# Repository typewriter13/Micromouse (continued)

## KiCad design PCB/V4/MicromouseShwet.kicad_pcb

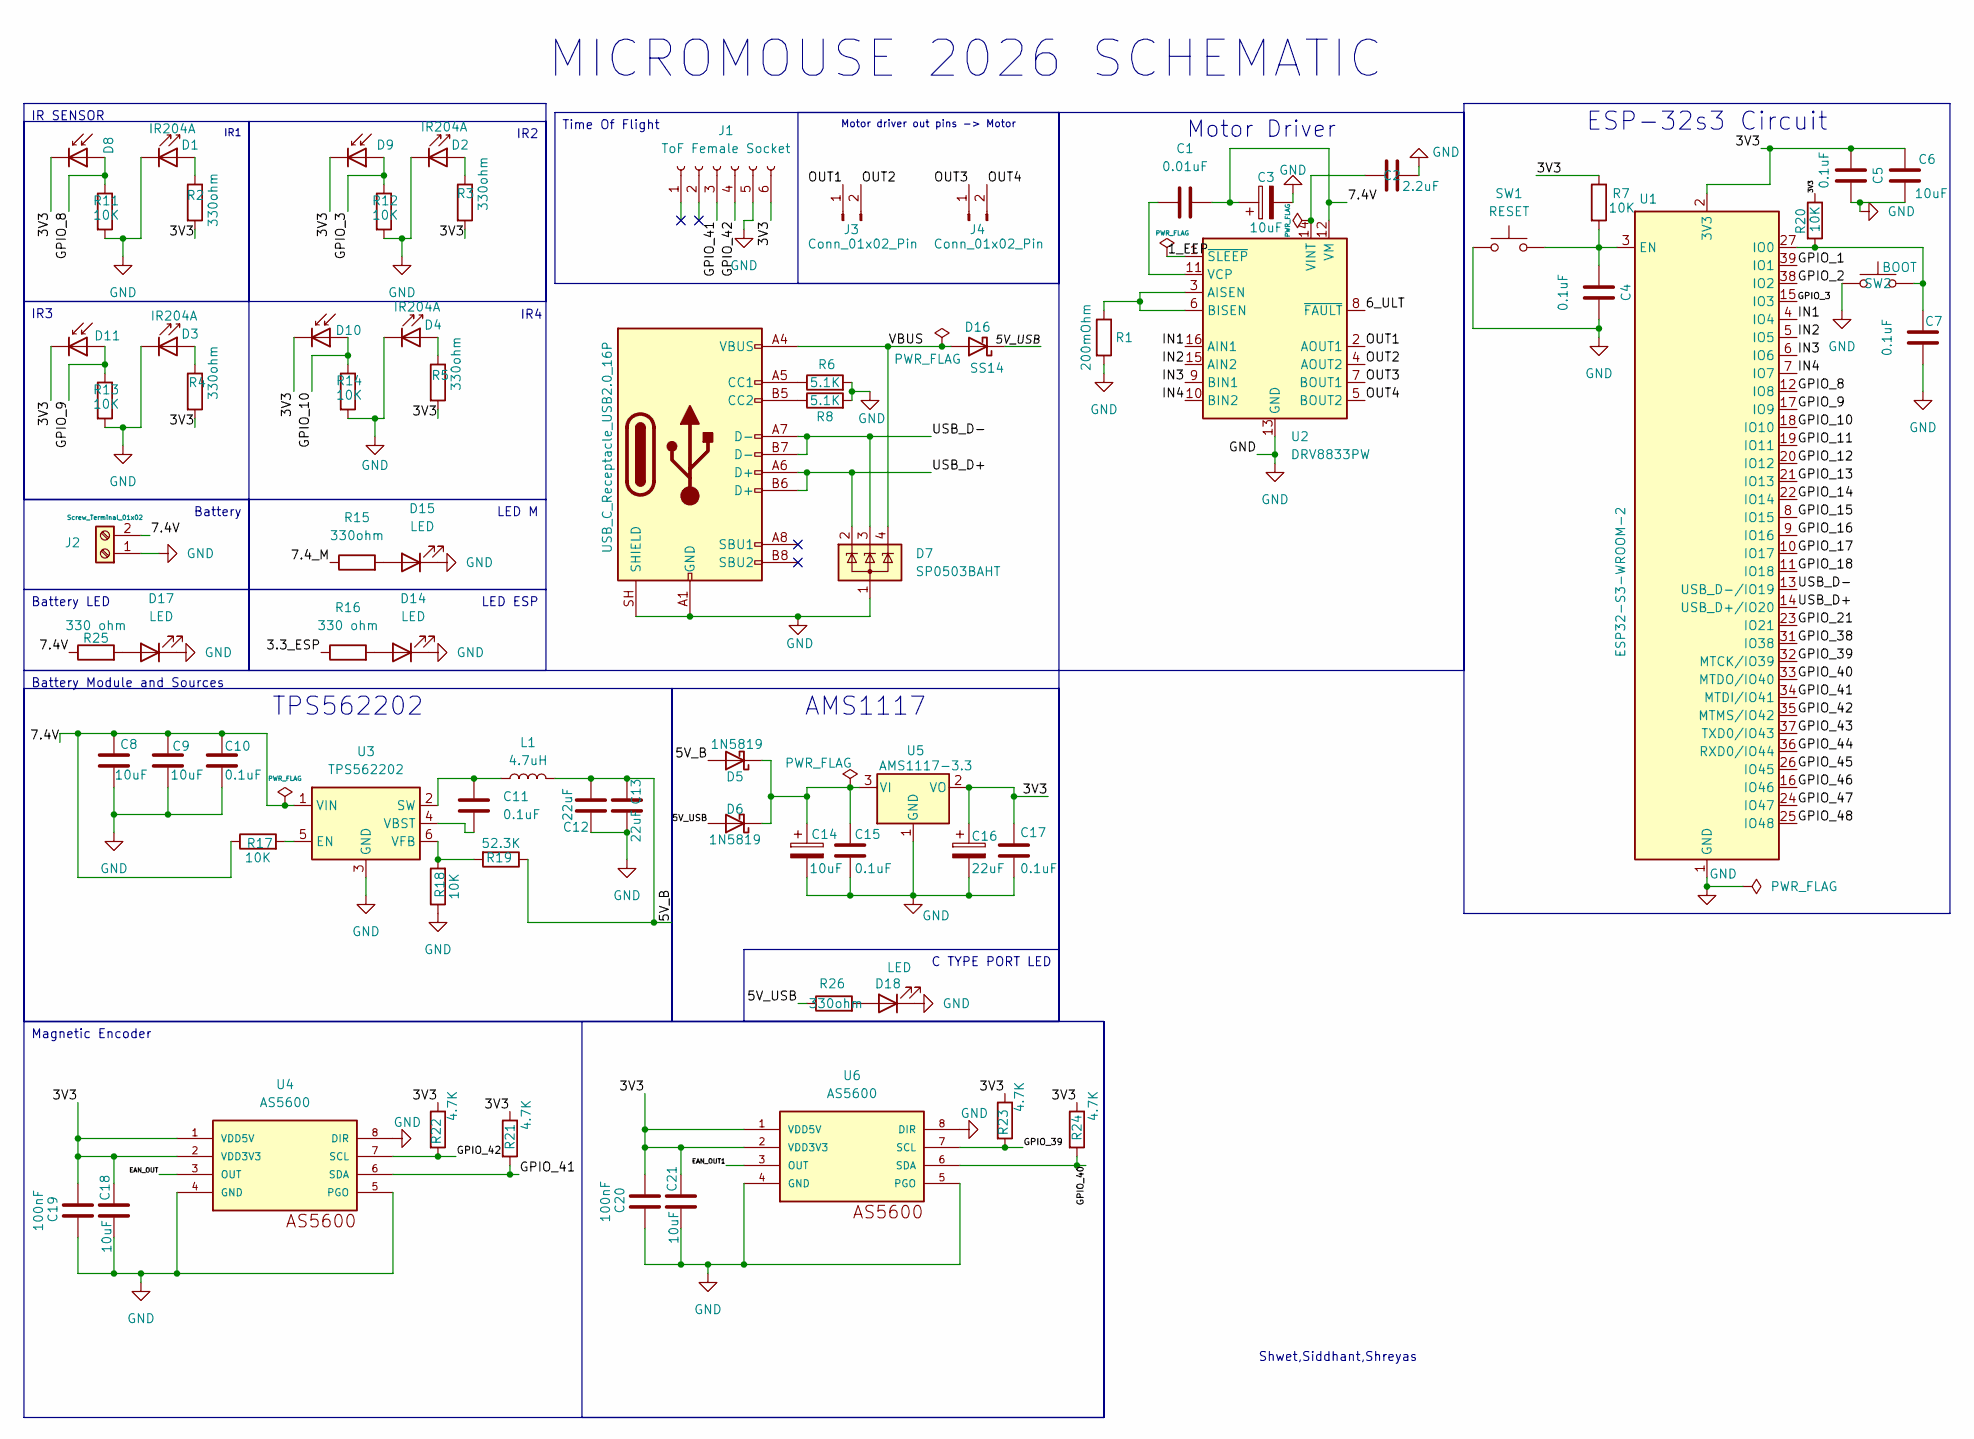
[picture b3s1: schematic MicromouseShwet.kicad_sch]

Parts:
C1: 0.01uF; C_0805_2012Metric
C2: 2.2uF; C_0805_2012Metric
C3, C6, C8, C9, C14, C18, C21: 10uF; C_0805_2012Metric
C4, C5, C7, C10, C11, C15, C17: 0.1uF; C_0805_2012Metric
C12, C13, C16: 22uF; C_0805_2012Metric
C19, C20: 100nF; C_0805_2012Metric
D1, D2, D3, D4: IR204A; LED_D3.0mm_IRBlack
D5, D6: 1N5819; D_3220_8050Metric
D7: SP0503BAHT; SOT-143
D8, D9, D10, D11: D_Photo; LED_D3.0mm
D14, D15, D17, D18: LED; LED_0805_2012Metric
D16: SS14; D_SMA
J1: ToF Female Socket; PinSocket_1x06_P1.00mm_Vertical_SMD_Pin1Left
J2: Screw_Terminal_01x02; JST_EH_S2B-EH_1x02_P2.50mm_Horizontal
J3, J4: Conn_01x02_Pin; JST_EH_S2B-EH_1x02_P2.50mm_Horizontal
J5: USB_C_Receptacle_USB2.0_16P; USB_C_Receptacle_GCT_USB4105-xx-A_16P_TopMnt_Horizontal
L1: 4.7uH; L_Sunlord_MWSA0603S
R1: 200mOhm; R_0805_2012Metric
R2, R3, R4, R5, R15, R26: 330ohm; R_0805_2012Metric
R6, R8: 5.1K; R_0805_2012Metric
R7, R11, R12, R13, R14, R17, R18, R20: 10K; R_0805_2012Metric
R16, R25: 330 ohm; R_0805_2012Metric
R19: 52.3K; R_0805_2012Metric
R21, R22, R23, R24: 4.7K; R_0805_2012Metric
SW1: RESET; SW_Push_SPST_NO_Alps_SKRK
SW2: BOOT; SW_Push_SPST_NO_Alps_SKRK
U1: ESP32-S3-WROOM-2
U2: DRV8833PW; TSSOP-16_4.4x5mm_P0.65mm
U3: TPS562202; SOT-563
U4, U6: AS5600; SOIC8
U5: AMS1117-3.3; SOT-223-3_TabPin2

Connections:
/1_EEP: U2.1 (~SLEEP)
/3.3_ESP: R16.1
/3V3: C5.2, C6.1, C16.1, C17.1, C18.1, C19.1, C20.1, C21.1, D8.1 (K), D9.1 (K), D10.1 (K), D11.1 (K), J1.6, R2.2, R3.2, R4.2, R5.2, R7.1, R20.1, R21.1, R22.1, R23.1, R24.1, U1.2 (3V3), U4.1 (VDD5V), U4.2 (VDD3V3), U5.2 (VO), U6.1 (VDD5V), U6.2 (VDD3V3)
/5V_B: C12.1, C13.1, D5.2 (A), L1.2, R19.1
/5V_USB: D6.2 (A), D16.1 (K), R26.1
/6_ULT: U2.8 (~FAULT)
/7.4V: C1.2, C3.1, C8.1, C9.1, C10.1, J2.2, R17.1, R25.1, U2.12 (VM), U3.1 (VIN)
/7.4_M: R15.1
/EAN_OUT: U4.3 (OUT)
/EAN_OUT1: U6.3 (OUT)
/GPIO_1: U1.39 (IO1)
/GPIO_2: U1.38 (IO2)
/GPIO_3: D9.2 (A), R12.1, U1.15 (IO3)
/GPIO_8: D8.2 (A), R11.1, U1.12 (IO8)
/GPIO_9: D11.2 (A), R13.1, U1.17 (IO9)
/GPIO_10: D10.2 (A), R14.1, U1.18 (IO10)
/GPIO_11: U1.19 (IO11)
/GPIO_12: U1.20 (IO12)
/GPIO_13: U1.21 (IO13)
/GPIO_14: U1.22 (IO14)
/GPIO_15: U1.8 (IO15)
/GPIO_16: U1.9 (IO16)
/GPIO_17: U1.10 (IO17)
/GPIO_18: U1.11 (IO18)
/GPIO_21: U1.23 (IO21)
/GPIO_38: U1.31 (IO38)
/GPIO_39: R23.2, U1.32 (MTCK/IO39), U6.7 (SCL)
/GPIO_40: R24.2, U1.33 (MTDO/IO40), U6.6 (SDA)
/GPIO_41: J1.3, R21.2, U1.34 (MTDI/IO41), U4.6 (SDA)
/GPIO_42: J1.4, R22.2, U1.35 (MTMS/IO42), U4.7 (SCL)
/GPIO_43: U1.37 (TXD0/IO43)
/GPIO_44: U1.36 (RXD0/IO44)
/GPIO_45: U1.26 (IO45)
/GPIO_46: U1.16 (IO46)
/GPIO_47: U1.24 (IO47)
/GPIO_48: U1.25 (IO48)
/IN1: U1.4 (IO4), U2.16 (AIN1)
/IN2: U1.5 (IO5), U2.15 (AIN2)
/IN3: U1.6 (IO6), U2.9 (BIN1)
/IN4: U1.7 (IO7), U2.10 (BIN2)
/OUT1: J3.1, U2.2 (AOUT1)
/OUT2: J3.2, U2.4 (AOUT2)
/OUT3: J4.1, U2.7 (BOUT1)
/OUT4: J4.2, U2.5 (BOUT2)
/USB_D+: D7.2 (K), J5.A6 (D+), J5.B6 (D+), U1.14 (USB_D+/IO20)
/USB_D-: D7.3 (K), J5.A7 (D-), J5.B7 (D-), U1.13 (USB_D-/IO19)
/VBUS: D7.4 (K), D16.2 (A), J5.A4 (VBUS), J5.A9 (VBUS), J5.B4 (VBUS), J5.B9 (VBUS)
GND: C2.2, C3.2, C4.1, C5.1, C6.2, C7.1, C8.2, C9.2, C10.2, C12.2, C13.2, C14.2, C15.2, C16.2, C17.2, C18.2, C19.2, C20.2, C21.2, D1.1 (K), D2.1 (K), D3.1 (K), D4.1 (K), D7.1 (A), D14.1 (K), D15.1 (K), D17.1 (K), D18.1 (K), J1.5, J2.1, J5.A1 (GND), J5.A12 (GND), J5.B1 (GND), J5.B12 (GND), J5.SH (SHIELD), R1.2, R6.2, R8.2, R11.2, R12.2, R13.2, R14.2, R18.1, SW1.1, SW2.1, U1.1 (GND), U1.40 (GND), U1.41 (GND), U2.13 (GND), U3.3 (GND), U4.4 (GND), U4.5 (PGO), U4.8 (DIR), U5.1 (GND), U6.4 (GND), U6.5 (PGO), U6.8 (DIR)
unnamed: D1.2 (A), R2.1
unnamed: D2.2 (A), R3.1
unnamed: D3.2 (A), R4.1
unnamed: D4.2 (A), R5.1
unnamed: C14.1, C15.1, D5.1 (K), D6.1 (K), U5.3 (VI)
unnamed: D14.2 (A), R16.2
unnamed: D15.2 (A), R15.2
unnamed: D17.2 (A), R25.2
unnamed: D18.2 (A), R26.2
unnamed: J5.A5 (CC1), R6.1
unnamed: J5.B5 (CC2), R8.1
unnamed: C4.2, R7.2, SW1.2, U1.3 (EN)
unnamed: C7.2, R20.2, SW2.2, U1.27 (IO0)
unnamed: R1.1, U2.3 (AISEN), U2.6 (BISEN)
unnamed: C1.1, U2.11 (VCP)
unnamed: C2.1, U2.14 (VINT)
unnamed: R17.2, U3.5 (EN)
unnamed: C11.1, L1.1, U3.2 (SW)
unnamed: C11.2, U3.4 (VBST)
unnamed: R18.2, R19.2, U3.6 (VFB)

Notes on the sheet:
MICROMOUSE 2026 SCHEMATIC
Shwet,Siddhant,Shreyas
IR4
Magnetic Encoder
ESP-32s3 Circuit
IR1
LED ESP
Battery Module and Sources
Motor driver out pins -> Motor
IR3
LED M
IR2
Battery LED
AMS1117
Battery
C TYPE PORT LED
Motor Driver
TPS562202
IR SENSOR
Time Of Flight

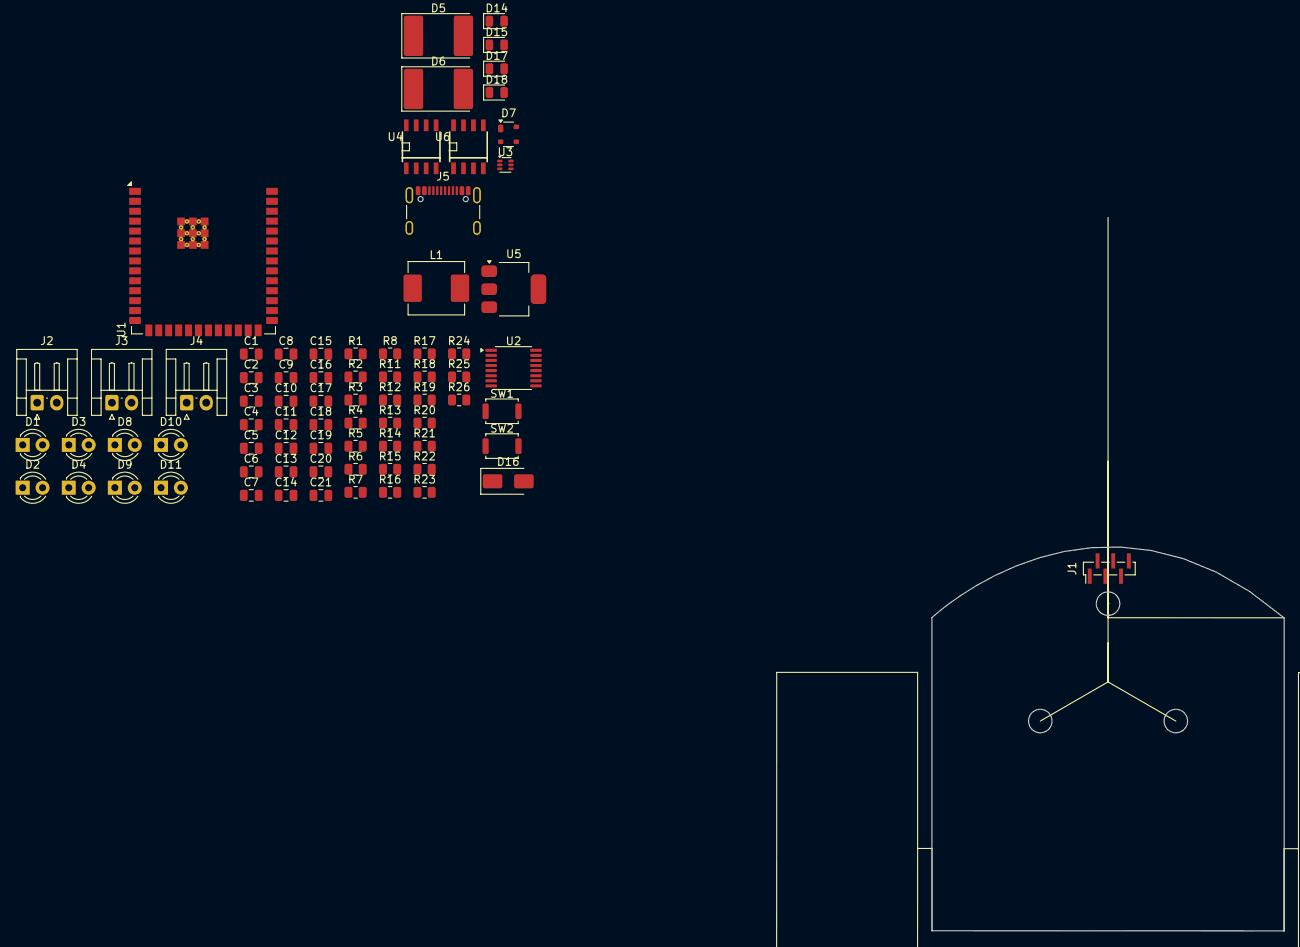
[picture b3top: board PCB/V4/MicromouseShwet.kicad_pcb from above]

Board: 2 copper layers, 45.0 x 49.0 mm, 75 parts (0 on the bottom side), 44 nets.

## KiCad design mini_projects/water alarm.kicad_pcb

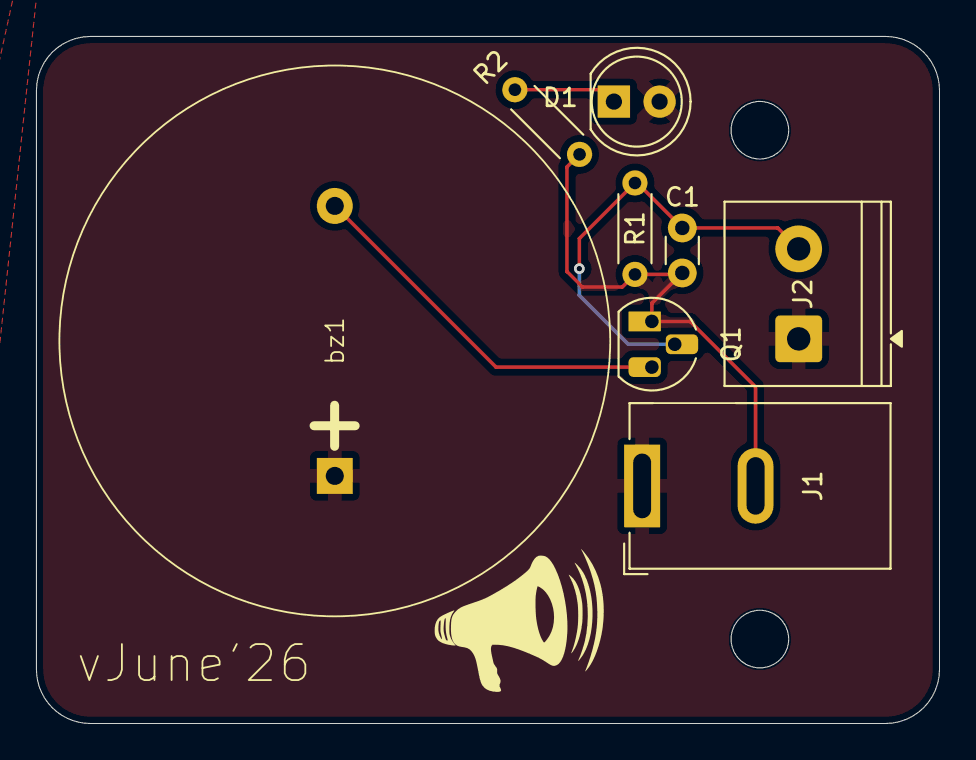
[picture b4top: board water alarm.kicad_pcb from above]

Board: 2 copper layers, 50.2 x 38.2 mm, 8 parts (0 on the bottom side), 5 nets.

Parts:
C1: 1nF; C_Disc_D3.0mm_W1.6mm_P2.50mm
D1: LED_Small_Filled; LED_D5.0mm
J1: Jack-DC; BarrelJack_GCT_DCJ200-10-A_Horizontal
J2: Screw_Terminal_01x02; TerminalBlock_Phoenix_PT-1,5-2-5.0-H_1x02_P5.00mm_Horizontal
Q1: 2N7000; TO-92_HandSolder
R1: 10M; R_Axial_DIN0204_L3.6mm_D1.6mm_P5.08mm_Horizontal
R2: 6.8K; R_Axial_DIN0204_L3.6mm_D1.6mm_P5.08mm_Horizontal
bz1: buzzer; Buzzer_D30mm_H20mm_P15mm_668-1652-ND_Al-3035-TT-12V-R

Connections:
/Gate: C1.1, J2.2, Q1.2 (G), R1.1
GND: C1.2, J1.2, Q1.1 (S), R1.2, R2.2
unnamed: D1.1 (K), R2.1
unnamed: Q1.3 (D), bz1.2 (-)
VCC: D1.2 (A), J1.1, J2.1, bz1.1 (+)

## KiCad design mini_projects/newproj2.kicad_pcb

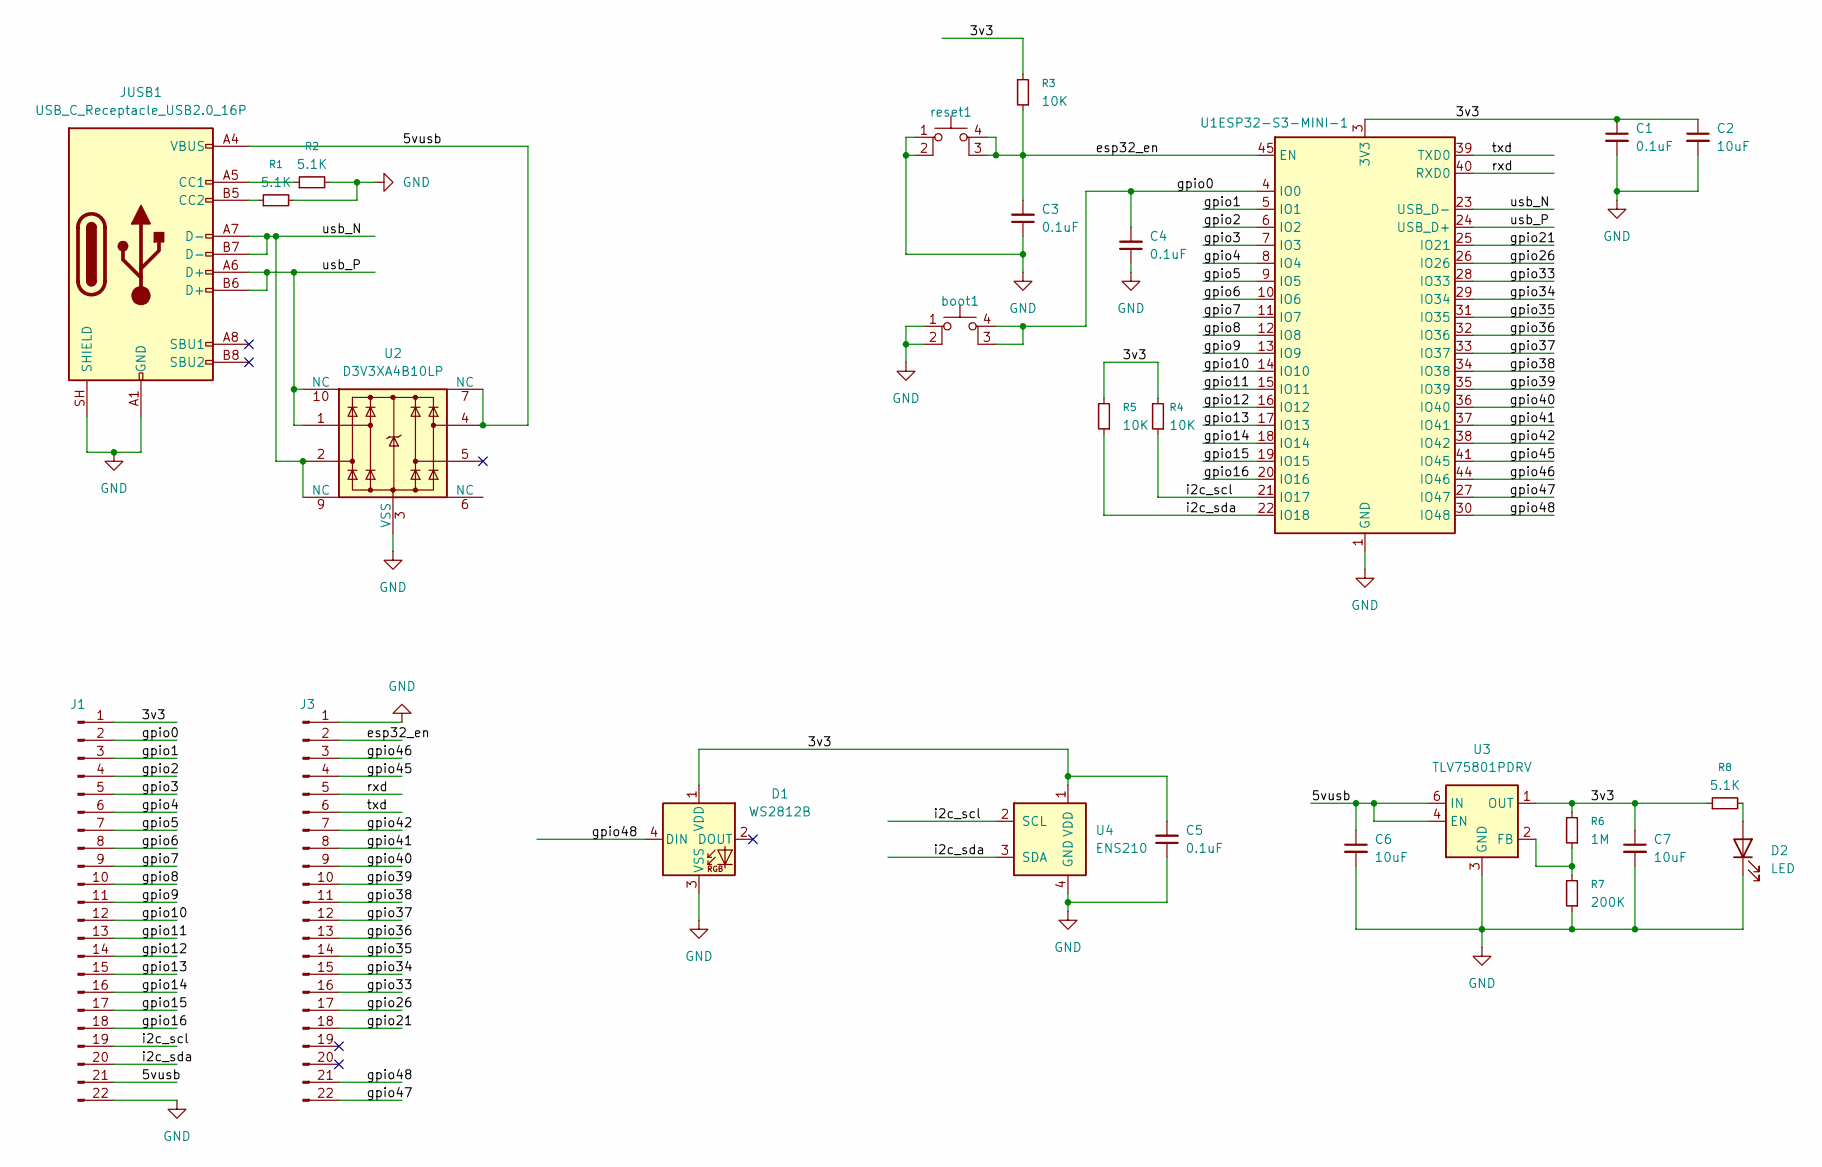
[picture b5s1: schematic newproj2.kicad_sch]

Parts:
C1, C3, C4, C5: 0.1uF; C_0603_1608Metric
C2, C6, C7: 10uF; C_0603_1608Metric
D1: WS2812B; LED_WS2812B_PLCC4_5.0x5.0mm_P3.2mm
D2: LED; LED_0603_1608Metric
J1, J3: Conn_01x22_Pin; PinHeader_1x22_P2.54mm_Vertical
JUSB1: USB_C_Receptacle_USB2.0_16P; USB_C_Receptacle_GCT_USB4105-xx-A_16P_TopMnt_Horizontal
R1, R2, R8: 5.1K; R_0603_1608Metric
R3, R4, R5: 10K; R_0603_1608Metric
R6: 1M; R_0603_1608Metric
R7: 200K; R_0603_1608Metric
U1: ESP32-S3-MINI-1; ESP32-S2-MINI-1
U2: D3V3XA4B10LP; Diodes_UDFN-10_1x2.5mm_P0.5mm
U3: TLV75801PDRV; WSON-6-1EP_2x2mm_P0.65mm_EP1x1.6mm
U4: ENS210; AMS_QFN-4-1EP_2x2mm_P0.95mm_EP0.7x1.6mm
boot1: SW_SPST_PTS810
reset1: SW_SPST_PTS810

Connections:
/5vusb: C6.1, J1.21, JUSB1.A4 (VBUS), JUSB1.A9 (VBUS), JUSB1.B4 (VBUS), JUSB1.B9 (VBUS), U2.4, U2.7 (NC), U3.4 (EN), U3.6 (IN)
/<NO NET>: C1.1, C2.1, C5.2, C7.1, D1.1 (VDD), J1.1, R3.2, R4.2, R5.2, R6.2, R8.1, U1.3 (3V3), U3.1 (OUT), U4.1 (VDD)
/esp32_en: C3.2, J3.2, R3.1, U1.45 (EN), reset1.3 (K), reset1.4 (A)
/gpio0: C4.2, J1.2, U1.4 (IO0), boot1.3 (K), boot1.4 (A)
/gpio1: J1.3, U1.5 (IO1)
/gpio2: J1.4, U1.6 (IO2)
/gpio3: J1.5, U1.7 (IO3)
/gpio4: J1.6, U1.8 (IO4)
/gpio5: J1.7, U1.9 (IO5)
/gpio6: J1.8, U1.10 (IO6)
/gpio7: J1.9, U1.11 (IO7)
/gpio8: J1.10, U1.12 (IO8)
/gpio9: J1.11, U1.13 (IO9)
/gpio10: J1.12, U1.14 (IO10)
/gpio11: J1.13, U1.15 (IO11)
/gpio12: J1.14, U1.16 (IO12)
/gpio13: J1.15, U1.17 (IO13)
/gpio14: J1.16, U1.18 (IO14)
/gpio15: J1.17, U1.19 (IO15)
/gpio16: J1.18, U1.20 (IO16)
/gpio21: J3.18, U1.25 (IO21)
/gpio26: J3.17, U1.26 (IO26)
/gpio33: J3.16, U1.28 (IO33)
/gpio34: J3.15, U1.29 (IO34)
/gpio35: J3.14, U1.31 (IO35)
/gpio36: J3.13, U1.32 (IO36)
/gpio37: J3.12, U1.33 (IO37)
/gpio38: J3.11, U1.34 (IO38)
/gpio39: J3.10, U1.35 (IO39)
/gpio40: J3.9, U1.36 (IO40)
/gpio41: J3.8, U1.37 (IO41)
/gpio42: J3.7, U1.38 (IO42)
/gpio45: J3.4, U1.41 (IO45)
/gpio46: J3.3, U1.44 (IO46)
/gpio47: J3.22, U1.27 (IO47)
/gpio48: D1.4 (DIN), J3.21, U1.30 (IO48)
/i2c_scl: J1.19, R4.1, U1.21 (IO17), U4.2 (SCL)
/i2c_sda: J1.20, R5.1, U1.22 (IO18), U4.3 (SDA)
/rxd: J3.5, U1.40 (RXD0)
/txd: J3.6, U1.39 (TXD0)
/usb_N: JUSB1.A7 (D-), JUSB1.B7 (D-), U1.23 (USB_D-), U2.2, U2.9 (NC)
/usb_P: JUSB1.A6 (D+), JUSB1.B6 (D+), U1.24 (USB_D+), U2.1, U2.10 (NC)
GND: C1.2, C2.2, C3.1, C4.1, C5.1, C6.2, C7.2, D1.3 (VSS), D2.1 (K), J1.22, J3.1, JUSB1.A1 (GND), JUSB1.A12 (GND), JUSB1.B1 (GND), JUSB1.B12 (GND), JUSB1.SH (SHIELD), R1.2, R2.2, R7.1, U1.1 (GND), U1.2 (GND), U1.42 (GND), U1.43 (GND), U1.46 (GND), U1.47 (GND), U1.48 (GND), U1.49 (GND), U1.50 (GND), U1.51 (GND), U1.52 (GND), U1.53 (GND), U1.54 (GND), U1.55 (GND), U1.56 (GND), U1.57 (GND), U1.58 (GND), U1.59 (GND), U1.60 (GND), U1.61 (GND), U1.62 (GND), U1.63 (GND), U1.64 (GND), U1.65 (GND), U2.3 (VSS), U2.8 (VSS), U3.3 (GND), U3.7 (GND), U4.4 (GND), U4.5 (GND), boot1.1, boot1.2, reset1.1, reset1.2
unnamed: D2.2 (A), R8.2
unnamed: JUSB1.A5 (CC1), R2.1
unnamed: JUSB1.B5 (CC2), R1.1
unnamed: R6.1, R7.2, U3.2 (FB)

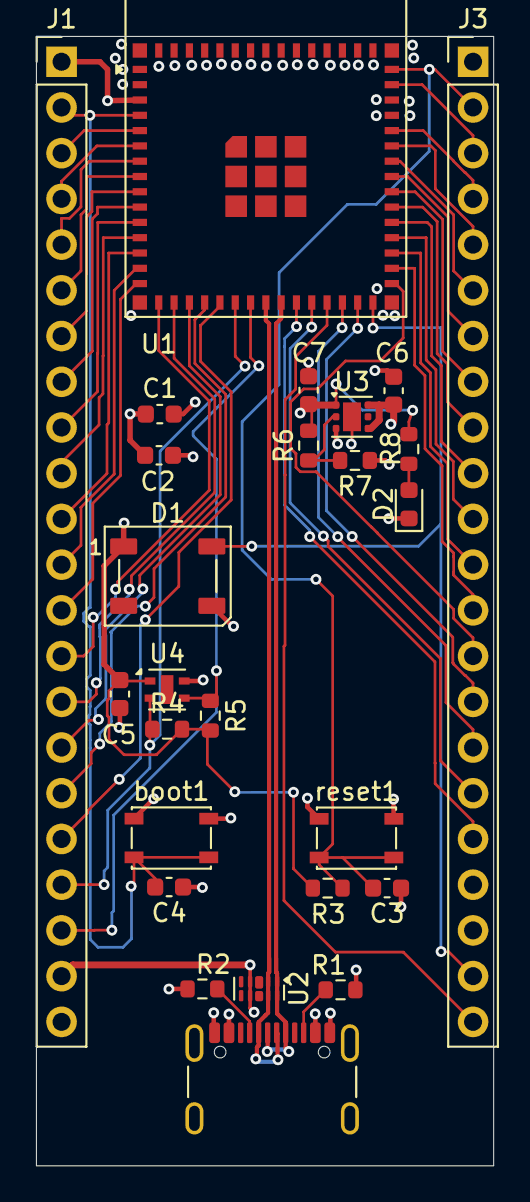
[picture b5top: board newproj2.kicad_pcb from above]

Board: 4 copper layers, 25.4 x 62.7 mm, 26 parts (0 on the bottom side), 47 nets.

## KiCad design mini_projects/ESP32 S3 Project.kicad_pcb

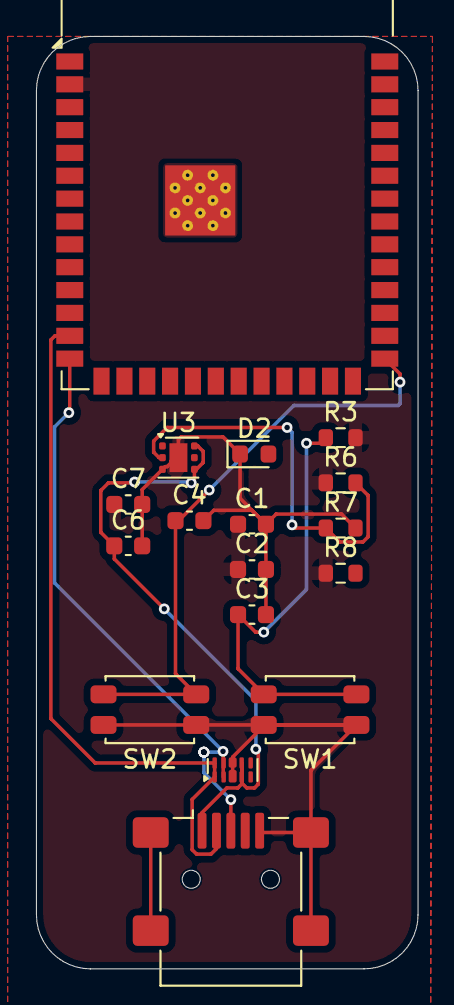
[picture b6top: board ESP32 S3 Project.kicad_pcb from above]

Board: 2 copper layers, 21.2 x 51.8 mm, 17 parts (0 on the bottom side), 9 nets.

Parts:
C1, C3, C4: 0.1uF; C_0603_1608Metric
C2, C6, C7: 10uF; C_0603_1608Metric
D2: LED; LED_0603_1608Metric
J1: USB_B_Micro; USB_Mini-B_Lumberg_2486_01_Horizontal
R3: 10k; R_0603_1608Metric
R6: 1M; R_0603_1608Metric
R7: 200K; R_0603_1608Metric
R8: 5.1K; R_0603_1608Metric
SW1: RESET; SW_SPST_EVQP2_MiddlePushTravel_H2.5mm
SW2: BOOT; SW_SPST_EVQP2_MiddlePushTravel_H2.5mm
U1: ESP32-S3-WROOM-1
U2: D3V3XA4B10LP; Diodes_UDFN-10_1x2.5mm_P0.5mm
U3: TLV75801PDRV; WSON-6-1EP_2x2mm_P0.65mm_EP1x1.6mm

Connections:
/3V3: C1.1, C2.1, C7.1, R3.2, R6.1, R8.1, U1.2 (3V3), U3.1 (OUT)
/5VUSB: C6.1, J1.1 (VBUS), U2.4, U2.7 (NC), U3.4 (EN), U3.6 (IN)
/ESP32_EN: C3.1, R3.1, SW1.2, U1.3 (EN)
/GPIO0: C4.1, SW2.2 (B), U1.27 (IO0)
/USB_N: J1.2 (D-), U1.13 (USB_D-), U2.1, U2.10 (NC)
/USB_P: J1.3 (D+), U1.14 (USB_D+), U2.2, U2.9 (NC)
GND: C1.2, C2.2, C3.2, C4.2, C6.2, C7.2, D2.1 (K), J1.5 (GND), J1.SH (Shield), R7.2, SW1.1, SW2.1 (A), U1.1 (GND), U1.40 (GND), U1.41 (GND), U2.3 (VSS), U2.8 (VSS), U3.3 (GND), U3.7 (GND)
unnamed: D2.2 (A), R8.2
unnamed: R6.2, R7.1, U3.2 (FB)

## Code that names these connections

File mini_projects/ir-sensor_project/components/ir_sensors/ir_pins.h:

/*
 * ir_pins.h
 *
 *  Created on: 12-Jul-2026
 *      Author: Siddhant Deshpande
 */

 #ifndef IR_PINS_H
 #define IR_PINS_H

 #include "hal/adc_types.h"

 #define IR1_CHANNEL ADC_CHANNEL_0   // GPIO36
 #define IR2_CHANNEL ADC_CHANNEL_1   // GPIO37
 #define IR3_CHANNEL ADC_CHANNEL_2   // GPIO38
 #define IR4_CHANNEL ADC_CHANNEL_3   // GPIO39
 #define IR5_CHANNEL ADC_CHANNEL_4   // GPIO32

 #endif

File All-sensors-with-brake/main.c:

#include <stdio.h>
#include "driver/i2c.h"
#include "driver/gpio.h"
#include "freertos/FreeRTOS.h"
#include "freertos/task.h"
#include "driver/mcpwm.h"
#include "soc/mcpwm_periph.h"
#include "esp_adc/adc_oneshot.h"
#include "esp_log.h"
#include "esp_err.h"
#include "sdkconfig.h"

static const char *TAG = "MICROMOUSE";

//I2C / ToF Definition
#define I2C_MASTER_NUM         I2C_NUM_0
#define I2C_MASTER_SDA_IO      41
#define I2C_MASTER_SCL_IO      42
#define I2C_MASTER_FREQ_HZ     100000

#define VL53L0X_ADDR           0x29
#define SYSRANGE_START_REG     0x00
#define RESULT_RANGE_REG       0x1E

#define LOWER_THRESHOLD        20
#define UPPER_THRESHOLD        2000

// Distance (mm) at which the bot should stop in front of a wall
#define WALL_STOP_DISTANCE_MM  200

//Motor Pin Definitions
#define MOTOR_PIN_0A 15
#define MOTOR_PIN_0B 16
#define MOTOR_PIN_1A 17
#define MOTOR_PIN_1B 18

#define MOTOR_DUTY_CYCLE       50.0

//ADC Definitions (4 IR sensors, all on ADC1)
#define ADC_PIN_1     ADC_CHANNEL_7   // GPIO8 Right Diagonal
#define ADC_PIN_2     ADC_CHANNEL_2   // GPIO3 Left Diagonal
#define ADC_PIN_3     ADC_CHANNEL_8   // GPIO9  Right
#define ADC_PIN_4     ADC_CHANNEL_9   // GPIO10 Left
#define ADC_UNIT      ADC_UNIT_1
#define ADC_BITWIDTH  ADC_BITWIDTH_12
#define ADC_ATTEN     ADC_ATTEN_DB_12

adc_oneshot_unit_handle_t adc_handle;

static bool motors_running = false;

//ToF

esp_err_t i2c_write_reg(uint8_t dev_addr, uint8_t reg, uint8_t data) {
    uint8_t write_buf[2] = {reg, data};
    return i2c_master_write_to_device(I2C_MASTER_NUM, dev_addr, write_buf, 2, 1000 / portTICK_PERIOD_MS);
}

esp_err_t i2c_read_reg(uint8_t dev_addr, uint8_t reg, uint8_t *data, size_t len) {
    return i2c_master_write_read_device(I2C_MASTER_NUM, dev_addr, &reg, 1, data, len, 1000 / portTICK_PERIOD_MS);
}

void tof_i2c_init(void) {
    i2c_config_t i2c_config = {
        .mode = I2C_MODE_MASTER,
        .sda_io_num = I2C_MASTER_SDA_IO,
        .scl_io_num = I2C_MASTER_SCL_IO,
        .sda_pullup_en = GPIO_PULLUP_ENABLE,
        .scl_pullup_en = GPIO_PULLUP_ENABLE,
        .master.clk_speed = I2C_MASTER_FREQ_HZ,
    };
    ESP_ERROR_CHECK(i2c_param_config(I2C_MASTER_NUM, &i2c_config));
    ESP_ERROR_CHECK(i2c_driver_install(I2C_MASTER_NUM, I2C_MODE_MASTER, 0, 0, 0));
    ESP_LOGI(TAG, "I2C initialized for ToF sensor.");
}

//Motor PWM

void initialize_pwm_gpio_pins()
{
    mcpwm_gpio_init(MCPWM_UNIT_0, MCPWM0A, MOTOR_PIN_0A);
    mcpwm_gpio_init(MCPWM_UNIT_0, MCPWM0B, MOTOR_PIN_0B);
    mcpwm_gpio_init(MCPWM_UNIT_0, MCPWM1A, MOTOR_PIN_1A);
    mcpwm_gpio_init(MCPWM_UNIT_0, MCPWM1B, MOTOR_PIN_1B);
}

void pwm_gpio_configuration()
{
    mcpwm_config_t pwm_config;
    pwm_config.frequency = 1000;
    pwm_config.cmpr_a = 0;
    pwm_config.cmpr_b = 0;
    pwm_config.counter_mode = MCPWM_UP_COUNTER;
    pwm_config.duty_mode = MCPWM_DUTY_MODE_0;
    mcpwm_init(MCPWM_UNIT_0, MCPWM_TIMER_0, &pwm_config);
    mcpwm_init(MCPWM_UNIT_0, MCPWM_TIMER_1, &pwm_config);
}

void pwm_motors_move(float duty_cycle)
{
    mcpwm_set_signal_low(MCPWM_UNIT_0, MCPWM_TIMER_0, MCPWM_OPR_B);
    mcpwm_set_duty(MCPWM_UNIT_0, MCPWM_TIMER_0, MCPWM_OPR_A, duty_cycle);
    mcpwm_set_duty_type(MCPWM_UNIT_0, MCPWM_TIMER_0, MCPWM_OPR_A, MCPWM_DUTY_MODE_0);

    mcpwm_set_signal_low(MCPWM_UNIT_0, MCPWM_TIMER_1, MCPWM_OPR_B);
    mcpwm_set_duty(MCPWM_UNIT_0, MCPWM_TIMER_1, MCPWM_OPR_A, duty_cycle);
    mcpwm_set_duty_type(MCPWM_UNIT_0, MCPWM_TIMER_1, MCPWM_OPR_A, MCPWM_DUTY_MODE_0);

    if (!motors_running) {
        ESP_LOGI(TAG, "Both motors running, synchronized.");
        motors_running = true;
    }
}

void pwm_motors_stop(void)
{
    // This is a hard brake
    mcpwm_set_signal_low(MCPWM_UNIT_0, MCPWM_TIMER_0, MCPWM_OPR_A);
    mcpwm_set_signal_low(MCPWM_UNIT_0, MCPWM_TIMER_0, MCPWM_OPR_B);
    mcpwm_set_signal_low(MCPWM_UNIT_0, MCPWM_TIMER_1, MCPWM_OPR_A);
    mcpwm_set_signal_low(MCPWM_UNIT_0, MCPWM_TIMER_1, MCPWM_OPR_B);

    if (motors_running) {
        ESP_LOGI(TAG, "Both motors braked — wall detected within %d mm.", WALL_STOP_DISTANCE_MM);
        motors_running = false;
    }
}

//IR Sensors

void initialize_adc()
{
    adc_oneshot_unit_init_cfg_t init_config = {
        .unit_id = ADC_UNIT,
        .clk_src = ADC_DIGI_CLK_SRC_DEFAULT,
    };
    ESP_ERROR_CHECK(adc_oneshot_new_unit(&init_config, &adc_handle));

    adc_oneshot_chan_cfg_t config = {
        .bitwidth = ADC_BITWIDTH,
        .atten = ADC_ATTEN,
    };
    ESP_ERROR_CHECK(adc_oneshot_config_channel(adc_handle, ADC_PIN_1, &config));
    ESP_ERROR_CHECK(adc_oneshot_config_channel(adc_handle, ADC_PIN_2, &config));
    ESP_ERROR_CHECK(adc_oneshot_config_channel(adc_handle, ADC_PIN_3, &config));
    ESP_ERROR_CHECK(adc_oneshot_config_channel(adc_handle, ADC_PIN_4, &config));
}

int read_adc(adc_channel_t channel)
{
    int adc_value;
    ESP_ERROR_CHECK(adc_oneshot_read(adc_handle, channel, &adc_value));
    return adc_value;
}

void i2c_scan(void)
{
    ESP_LOGI(TAG, "Starting I2C bus scan...");
    int found = 0;
    for (uint8_t addr = 1; addr < 127; addr++) {
        i2c_cmd_handle_t cmd = i2c_cmd_link_create();
        i2c_master_start(cmd);
        i2c_master_write_byte(cmd, (addr << 1) | I2C_MASTER_WRITE, true);
        i2c_master_stop(cmd);
        esp_err_t ret = i2c_master_cmd_begin(I2C_MASTER_NUM, cmd, 50 / portTICK_PERIOD_MS);
        i2c_cmd_link_delete(cmd);

        if (ret == ESP_OK) {
            ESP_LOGI(TAG, "Found device at address 0x%02X", addr);
            found++;
        }
    }
    if (found == 0) {
        ESP_LOGW(TAG, "No I2C devices found on the bus.");
    } else {
        ESP_LOGI(TAG, "Scan complete. %d device(s) found.", found);
    }
}

void app_main(void)
{
    tof_i2c_init();
	i2c_scan();
    initialize_adc();
    initialize_pwm_gpio_pins();
    pwm_gpio_configuration();

    uint8_t model_id;
    if (i2c_read_reg(VL53L0X_ADDR, 0xC0, &model_id, 1) != ESP_OK) {
        ESP_LOGE(TAG, "ToF Sensor failed to respond at address 0x29! Check I2C wiring.");
    } else {
        ESP_LOGI(TAG, "ToF Sensor detected successfully.");
    }

    uint16_t tof_distance_mm = 0;
    uint8_t dist_data[2];

    while (1)
    {
        int adc_value_1 = read_adc(ADC_PIN_1);
        int adc_value_2 = read_adc(ADC_PIN_2);
        int adc_value_3 = read_adc(ADC_PIN_3);
        int adc_value_4 = read_adc(ADC_PIN_4);

        i2c_write_reg(VL53L0X_ADDR, SYSRANGE_START_REG, 0x01);
        vTaskDelay(50 / portTICK_PERIOD_MS);

        if (i2c_read_reg(VL53L0X_ADDR, RESULT_RANGE_REG, dist_data, 2) == ESP_OK) {
            tof_distance_mm = ((dist_data[0] << 8) | dist_data[1]) / 2;
        } else {
            tof_distance_mm = 0;
        }

        // Decide whether to move or stop based on wall distance
        if (tof_distance_mm > LOWER_THRESHOLD && tof_distance_mm < UPPER_THRESHOLD) {
            if (tof_distance_mm <= WALL_STOP_DISTANCE_MM) {
                pwm_motors_stop();
            } else {
                pwm_motors_move(MOTOR_DUTY_CYCLE);
            }
            ESP_LOGI(TAG, "ToF Distance: %d mm", tof_distance_mm);
        } else {
            // Invalid/out-of-range reading — treat as no wall detected, keep moving
            pwm_motors_move(MOTOR_DUTY_CYCLE);
            ESP_LOGW(TAG, "ToF Distance: Out of Range / Invalid Reading");
        }

        ESP_LOGI(TAG, "IR1: %d  IR2: %d  IR3: %d  IR4: %d",
                 adc_value_1, adc_value_2, adc_value_3, adc_value_4);
        printf("-----------------------------------------------------------------\n");

        vTaskDelay(100 / portTICK_PERIOD_MS);
    }
}
